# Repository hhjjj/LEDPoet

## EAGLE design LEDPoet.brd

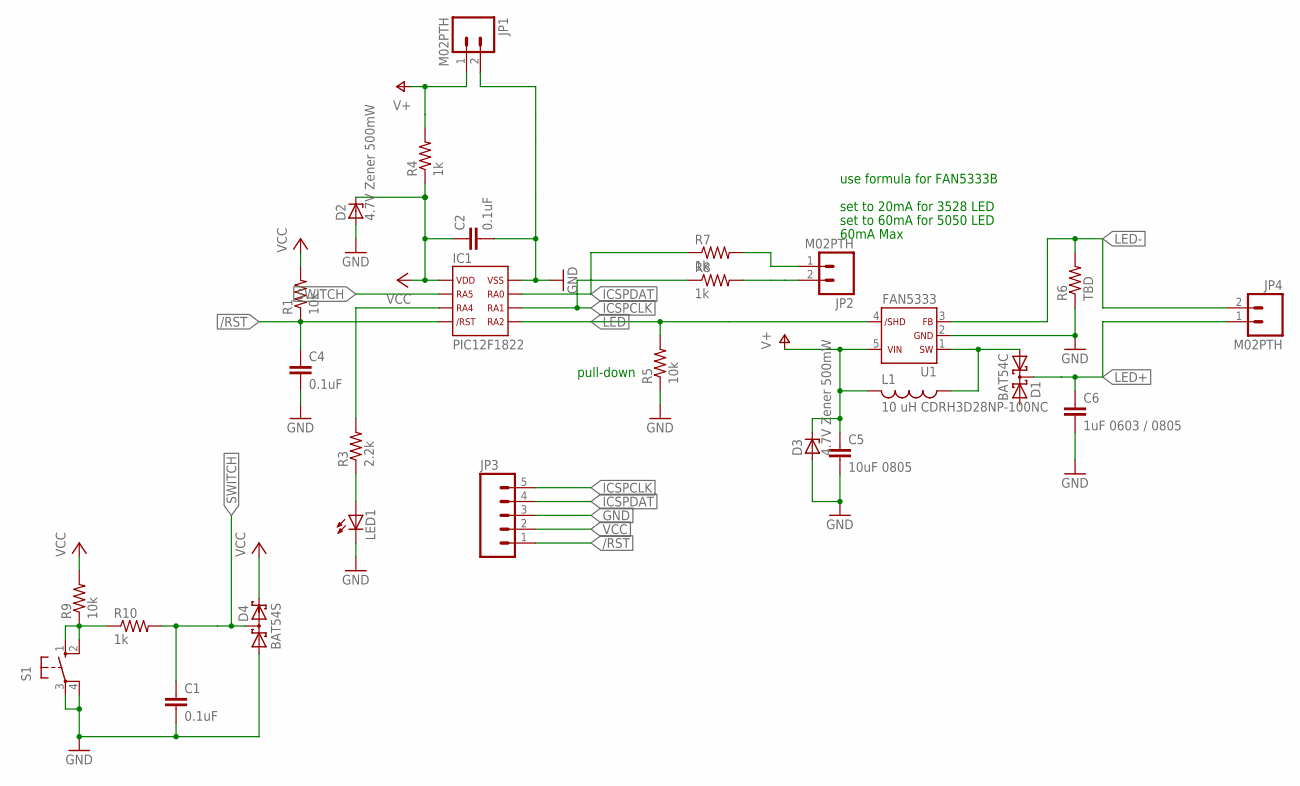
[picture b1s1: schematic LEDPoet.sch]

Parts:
C1, C2, C4: 0.1uF; C0603(1608)
C5: 10uF 0805; C0805(2012)
C6: 1uF 0603 / 0805; C0805(2012)
D1: BAT54C; SOT23
D2, D3: 4.7V Zener 500mW; SOD-123
D4: BAT54S; SOT23
IC1: PIC12F1822; SO8
JP1, JP2, JP4: M02PTH; 1X02
JP3: M05PTH; 1X05
L1: 10 uH CDRH3D28NP-100NC; CDRH3D18
LED1: LED0603; LED-0603
R1, R5, R9: 10k; R0603(1608)
R3: 2.2k; R0603(1608)
R4, R7, R8, R10: 1k; R0603(1608)
R6: TBD; R0603(1608)
S1: 40-XX; B3F-40XX
U1: FAN5333; SOT-23-5

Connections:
/RST: C4.1, IC1.4, JP3.1, R1.1
GND: C1.2, C2.2, C4.2, C5.2, C6.2, D2.A, D3.A, D4.1 (A1), IC1.8, JP1.2, JP3.3, LED1.C, R5.1, R6.1, S1.3, S1.4 (P1), U1.2
ICSPCLK: IC1.6, JP3.5, R8.1
ICSPDAT: IC1.7, JP3.4, R7.1
LED: IC1.5, R5.2, U1.4
LED+: C6.1, D1.3 (CC), JP4.1
LED-: JP4.2, R6.2, U1.3
unnamed: LED1.A, R3.1
unnamed: IC1.3, R3.2
unnamed: JP2.1, R7.2
unnamed: D1.1 (A1), L1.P$1 (1), U1.1
unnamed: R9.1, R10.1, S1.1 (S), S1.2 (S1)
unnamed: JP2.2, R8.2
SWITCH: C1.1, D4.3 (C1A2), IC1.2, R10.2
V+: C5.1, D3.C, JP1.1, L1.P$2 (2), R4.2, U1.5
VCC: C2.1, D2.C, D4.2 (C2), IC1.1, JP3.2, R1.2, R4.1, R9.2

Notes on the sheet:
set to 20mA for 3528 LED
set to 60mA for 5050 LED
60mA Max
use formula for FAN5333B
pull-down

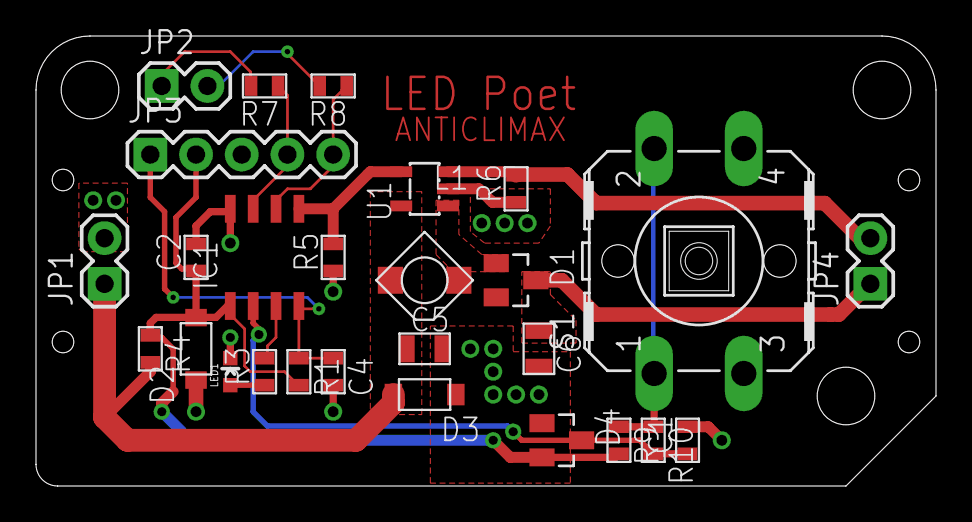
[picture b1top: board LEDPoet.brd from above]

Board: 2 copper layers, 50.0 x 25.0 mm, 27 parts (0 on the bottom side), 16 nets.

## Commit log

2013-11-21 LED poet for ANTICLIMAX Show
2013-11-22 gerber done
2013-12-30 backup

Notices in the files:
parts and their libraries:
SparkFun: Licensing: CC v3.0 Share-Alike You are welcome to use this library for commercial purposes.
